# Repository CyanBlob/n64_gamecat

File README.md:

# N64 GameCat

This is a free, open-source implementation of a Nintendo 64 cheating device, akin to the GameShark. It's currently based around the Kendryte K210 SoC (using the Sipeed MAiX BiT breakout), which I chose due to the high number of configurable IO (the N64 cartridge has 50 pins, though many of those aren't necessary for this project). I may eventually add support for ESP32 chips to the GameCat as well.

## Building
This is a PlatformIO project (https://platformio.org/), so building and uploading are relatively straightforward. Simply install PlatformIO (and make sure to add it to your $PATH), and then run `platformio run --target upload --target monitor` with the MAiX BiT plugged in. If it complains about `udev` rules, follow the link it provides.

## Circuits/schematics
I have some test PCBs on order (files are in the `/pcb` directory, made with KiCad EDA). Once I get the design for those finalized it should be as simple as ordering a PCB, soldering the MCU on, and soldering on a cartridge slot
#### Note:
When ordering a cartridge slot, it's important to get one with 2.5mm pin spacing. I've seen several only with 2.54mm spacing, which may not work on this PCB (or with the cartridges in general). I'm using this $2.50 version from AliExpress: https://www.aliexpress.com/item/33002915153.html?spm=a2g0s.9042311.0.0.1ec84c4dN5ezxJ

## FAQ
### Why do this?
I was bored, and that's literally the only reason. If you want to cheat at N64 games, you're likely much better off with an emulator.

### I looked at the PCB. Won't the cartridge end up being parallel with the console if I solder the cartridge slot on it?
Yes.
### Why?
I have no idea what I'm doing.

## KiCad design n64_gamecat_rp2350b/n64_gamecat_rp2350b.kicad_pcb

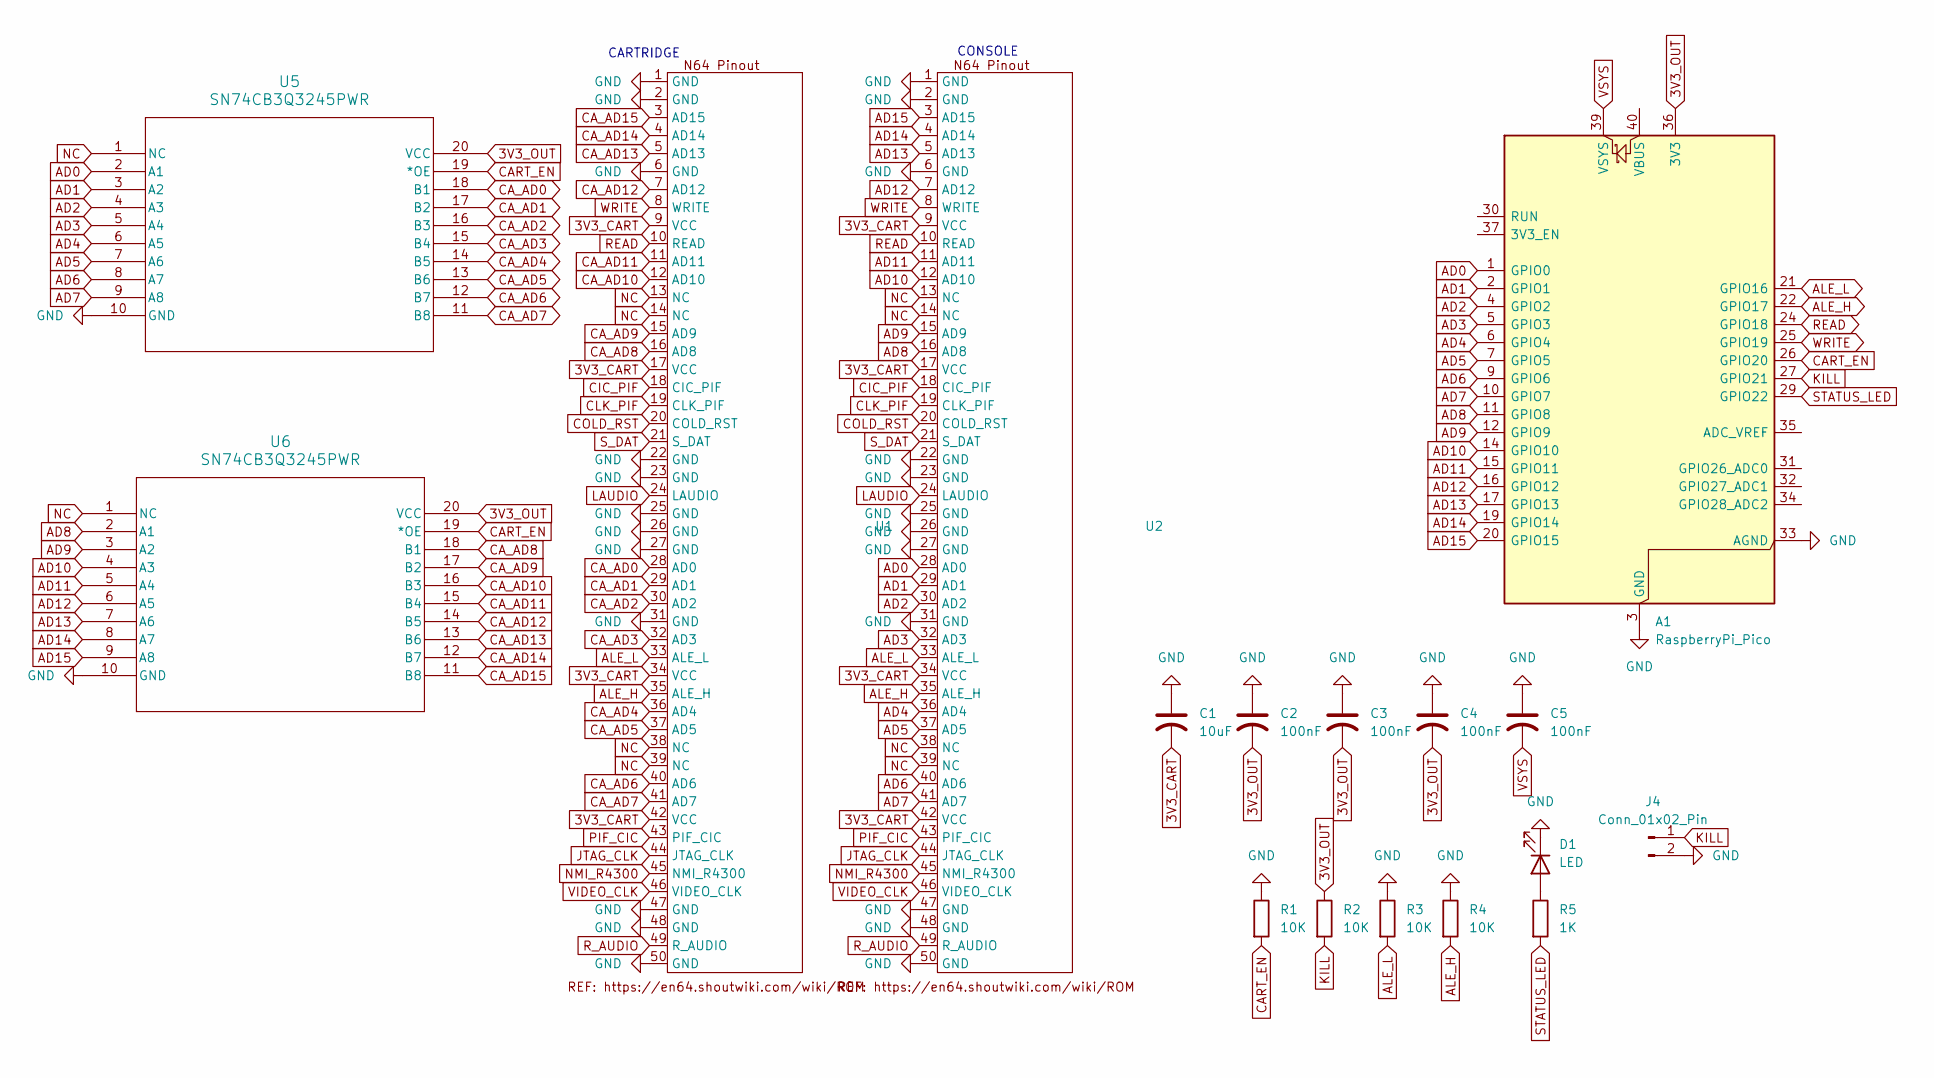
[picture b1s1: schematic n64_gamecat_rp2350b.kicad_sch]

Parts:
A1: RaspberryPi_Pico; RaspberryPi_Pico_Common_Unspecified
C1: 10uF; C_0805_2012Metric
C2, C3, C4, C5: 100nF; C_0402_1005Metric
D1: LED; LED_0402_1005Metric
J4: Conn_01x02_Pin; PinHeader_1x02_P2.54mm_Vertical
R1, R2, R3, R4: 10K; R_0402_1005Metric
R5: 1K; R_0402_1005Metric
U1: N64_cartridge_connecter_2.5mm
U2: N64_cartridge_pins_2.5mm
U5, U6: SN74CB3Q3245PWR; PW20

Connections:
3V3_CART: C1.2, U1.9 (VCC), U1.17 (VCC), U1.34 (VCC), U1.42 (VCC), U2.9 (VCC), U2.17 (VCC), U2.34 (VCC), U2.42 (VCC)
3V3_OUT: A1.36 (3V3), C2.2, C3.2, C4.2, R2.1, U5.20 (VCC), U6.20 (VCC)
AD0: A1.1 (GPIO0), U2.28 (AD0), U5.2 (A1)
AD1: A1.2 (GPIO1), U2.29 (AD1), U5.3 (A2)
AD2: A1.4 (GPIO2), U2.30 (AD2), U5.4 (A3)
AD3: A1.5 (GPIO3), U2.32 (AD3), U5.5 (A4)
AD4: A1.6 (GPIO4), U2.36 (AD4), U5.6 (A5)
AD5: A1.7 (GPIO5), U2.37 (AD5), U5.7 (A6)
AD6: A1.9 (GPIO6), U2.40 (AD6), U5.8 (A7)
AD7: A1.10 (GPIO7), U2.41 (AD7), U5.9 (A8)
AD8: A1.11 (GPIO8), U2.16 (AD8), U6.2 (A1)
AD9: A1.12 (GPIO9), U2.15 (AD9), U6.3 (A2)
AD10: A1.14 (GPIO10), U2.12 (AD10), U6.4 (A3)
AD11: A1.15 (GPIO11), U2.11 (AD11), U6.5 (A4)
AD12: A1.16 (GPIO12), U2.7 (AD12), U6.6 (A5)
AD13: A1.17 (GPIO13), U2.5 (AD13), U6.7 (A6)
AD14: A1.19 (GPIO14), U2.4 (AD14), U6.8 (A7)
AD15: A1.20 (GPIO15), U2.3 (AD15), U6.9 (A8)
ALE_H: A1.22 (GPIO17), R4.2, U1.35 (ALE_H), U2.35 (ALE_H)
ALE_L: A1.21 (GPIO16), R3.2, U1.33 (ALE_L), U2.33 (ALE_L)
CART_EN: A1.26 (GPIO20), R1.2, U5.19 (*OE), U6.19 (*OE)
CA_AD0: U1.28 (AD0), U5.18 (B1)
CA_AD1: U1.29 (AD1), U5.17 (B2)
CA_AD2: U1.30 (AD2), U5.16 (B3)
CA_AD3: U1.32 (AD3), U5.15 (B4)
CA_AD4: U1.36 (AD4), U5.14 (B5)
CA_AD5: U1.37 (AD5), U5.13 (B6)
CA_AD6: U1.40 (AD6), U5.12 (B7)
CA_AD7: U1.41 (AD7), U5.11 (B8)
CA_AD8: U1.16 (AD8), U6.18 (B1)
CA_AD9: U1.15 (AD9), U6.17 (B2)
CA_AD10: U1.12 (AD10), U6.16 (B3)
CA_AD11: U1.11 (AD11), U6.15 (B4)
CA_AD12: U1.7 (AD12), U6.14 (B5)
CA_AD13: U1.5 (AD13), U6.13 (B6)
CA_AD14: U1.4 (AD14), U6.12 (B7)
CA_AD15: U1.3 (AD15), U6.11 (B8)
CIC_PIF: U1.18 (CIC_PIF), U2.18 (CIC_PIF)
CLK_PIF: U1.19 (CLK_PIF), U2.19 (CLK_PIF)
COLD_RST: U1.20 (COLD_RST), U2.20 (COLD_RST)
GND: A1.3 (GND), A1.8 (GND), A1.13 (GND), A1.18 (GND), A1.23 (GND), A1.28 (GND), A1.33 (AGND), A1.38 (GND), C1.1, C2.1, C3.1, C4.1, C5.1, D1.1 (K), J4.2, R1.1, R3.1, R4.1, U1.1 (GND), U1.2 (GND), U1.6 (GND), U1.22 (GND), U1.23 (GND), U1.25 (GND), U1.26 (GND), U1.27 (GND), U1.31 (GND), U1.47 (GND), U1.48 (GND), U1.50 (GND), U2.1 (GND), U2.2 (GND), U2.6 (GND), U2.22 (GND), U2.23 (GND), U2.25 (GND), U2.26 (GND), U2.27 (GND), U2.31 (GND), U2.47 (GND), U2.48 (GND), U2.50 (GND), U5.10 (GND), U6.10 (GND)
JTAG_CLK: U1.44 (JTAG_CLK), U2.44 (JTAG_CLK)
KILL: A1.27 (GPIO21), J4.1, R2.2
LAUDIO: U1.24 (LAUDIO), U2.24 (LAUDIO)
NC: U1.13 (NC), U1.14 (NC), U1.38 (NC), U1.39 (NC), U2.13 (NC), U2.14 (NC), U2.38 (NC), U2.39 (NC), U5.1 (NC), U6.1 (NC)
NMI_R4300: U1.45 (NMI_R4300), U2.45 (NMI_R4300)
unnamed: D1.2 (A), R5.1
PIF_CIC: U1.43 (PIF_CIC), U2.43 (PIF_CIC)
READ: A1.24 (GPIO18), U1.10 (READ), U2.10 (READ)
R_AUDIO: U1.49 (R_AUDIO), U2.49 (R_AUDIO)
STATUS_LED: A1.29 (GPIO22), R5.2
S_DAT: U1.21 (S_DAT), U2.21 (S_DAT)
VIDEO_CLK: U1.46 (VIDEO_CLK), U2.46 (VIDEO_CLK)
VSYS: A1.39 (VSYS), C5.2
WRITE: A1.25 (GPIO19), U1.8 (WRITE), U2.8 (WRITE)

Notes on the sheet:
CONSOLE
CARTRIDGE

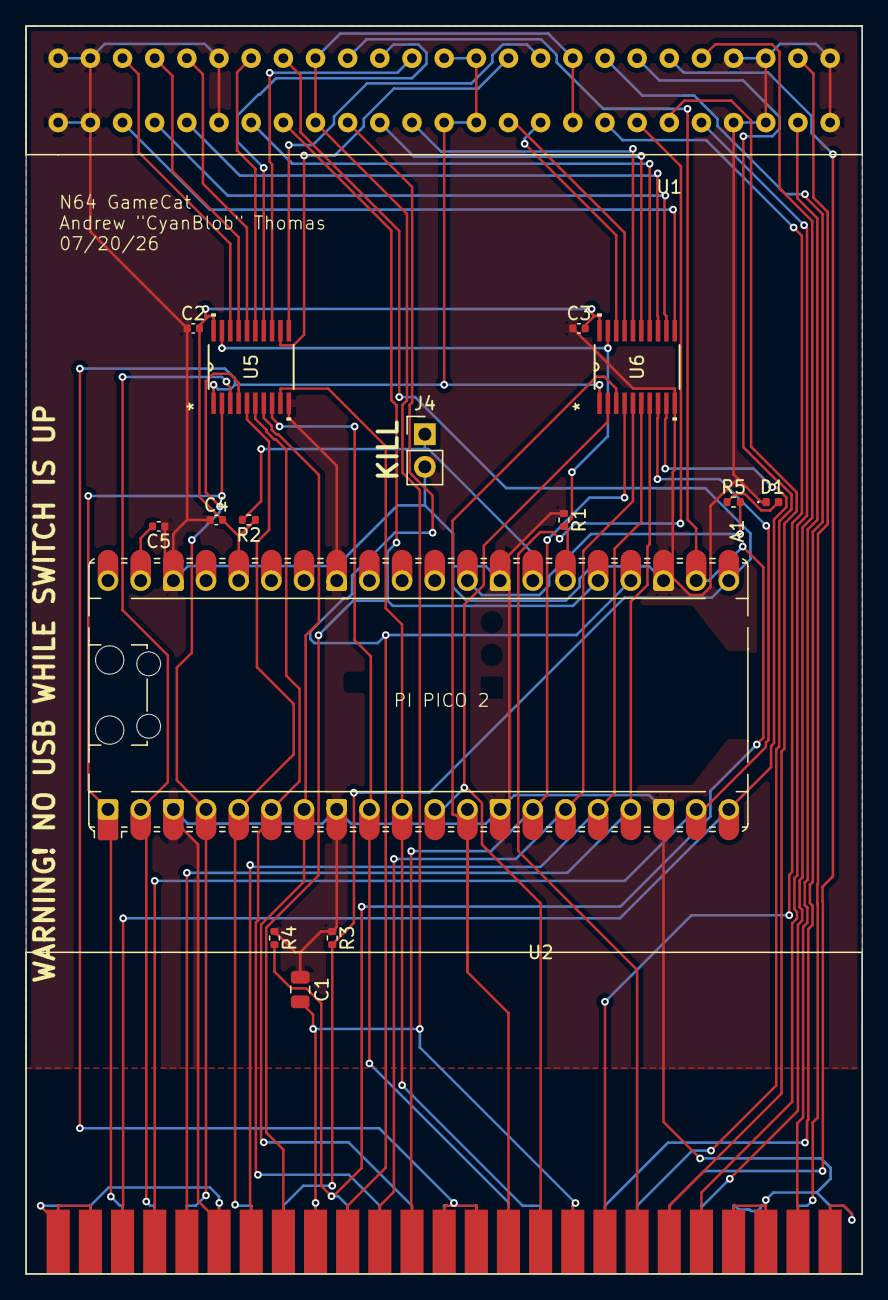
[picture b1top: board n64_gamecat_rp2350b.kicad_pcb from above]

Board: 2 copper layers, 65.0 x 97.0 mm, 17 parts (0 on the bottom side), 55 nets.

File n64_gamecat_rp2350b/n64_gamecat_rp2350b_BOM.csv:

"Id";"Designator";"Footprint";"Quantity";"Designation";"Supplier and ref";
1;"A1";"RaspberryPi_Pico_Common_Unspecified";1;"RaspberryPi_Pico";;;
2;"C1";"C_0805_2012Metric";1;"10uF";;;
3;"C2, C3, C4, C5";"C_0402_1005Metric";4;"100nF";;;
4;"D1";"LED_0402_1005Metric";1;"LED";;;
5;"J4";"PinHeader_1x02_P2.54mm_Vertical";1;"Conn_01x02_Pin";;;
6;"R1, R2, R3, R4";"R_0402_1005Metric";4;"10K";;;
7;"R5";"R_0402_1005Metric";1;"1K";;;
8;"SW1";"PinSocket_1x03_P2.54mm_Vertical";1;"SW_SPDT";;;
9;"U1";"N64_cartridge_connecter_2.5mm";1;"~";;;
10;"U2";"N64_cartridge_pins_2.5mm";1;"~";;;
11;"U3, U4";"DW20";2;"SN74CBTLV3245ADW";;;

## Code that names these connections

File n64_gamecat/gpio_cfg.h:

#ifndef N64_GAMECAT_GPIO_CFG_H
#define N64_GAMECAT_GPIO_CFG_H

#define PIN_MIN  2
#define PIN_MAX  39

#define CA_AD0  2
#define CA_AD1  3
#define CA_AD2  4
#define CA_AD3  5
#define CA_AD4  6
#define CA_AD5  7
#define CA_AD6  8
#define CA_AD7  9
#define CA_AD8  10
#define CA_AD9  11
#define CA_AD10 12
#define CA_AD11 13
#define CA_AD12 14
#define CA_AD13 15
#define CA_AD14 16
#define CA_AD15 17

#define CO_AD0  18
#define CO_AD1  19
#define CO_AD2  20
#define CO_AD3  21
#define CO_AD4  22
#define CO_AD5  23
#define CO_AD6  24
#define CO_AD7  25
#define CO_AD8  26
#define CO_AD9  27
#define CO_AD10 28
#define CO_AD11 29
#define CO_AD12 30
#define CO_AD13 31
#define CO_AD14 32
#define CO_AD15 33

uint console_pins[] = {

        CO_AD0,
        CO_AD1,
        CO_AD2,
        CO_AD3,
        CO_AD4,
        CO_AD5,
        CO_AD6,
        CO_AD7,
        CO_AD8,
        CO_AD9,
        CO_AD10,
        CO_AD11,
        CO_AD12,
        CO_AD13,
        CO_AD14,
        CO_AD15,
};
uint cartridge_pins[] = {
        CA_AD0,
        CA_AD1,
        CA_AD2,
        CA_AD3,
        CA_AD4,
        CA_AD5,
        CA_AD6,
        CA_AD7,
        CA_AD8,
        CA_AD9,
        CA_AD10,
        CA_AD11,
        CA_AD12,
        CA_AD13,
        CA_AD14,
        CA_AD15,
};

#define ALE_H 34
#define ALE_L 35
#define WRITE 36
#define READ  37

#define FLAG_ALE_H 40
#define FLAG_ALE_L 41
#define FLAG_WRITE 42
#define FLAG_READ 43

#endif //N64_GAMECAT_GPIO_CFG_H

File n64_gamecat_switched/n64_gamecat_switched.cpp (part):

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
/* ========= Pin mapping ========= */
#define AD_BASE         0   // GPIO N..N+15 -> AD[0..15]
#define CART_EN_PIN     20   // sideset to CBT OE/EN (1=connected, 0=isolated)
#define KILL_PIN        21   // pull low to force pass-through
#define STATUS_LED_PIN  22   // D1 on the schematic (heartbeat)

#define ALE_L_PIN_REL   16
#define ALE_H_PIN_REL   17
#define READ_N_PIN_REL  18
#define WRITE_N_PIN_REL 19
#define ALE_L_GPIO      (AD_BASE + ALE_L_PIN_REL)
#define ALE_H_GPIO      (AD_BASE + ALE_H_PIN_REL)
#define READ_N_GPIO     (AD_BASE + READ_N_PIN_REL)
#define WRITE_N_GPIO    (AD_BASE + WRITE_N_PIN_REL)

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    #if DEBUG_PRINT
    printf("heartbeat: %d\n", state);
    #endif
    gpio_put(STATUS_LED_PIN, state);
    return true; // keep firing
}

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
int main_dumb() {
    stdio_init_all();
    gpio_init(CART_EN_PIN);
    gpio_set_dir(CART_EN_PIN, true);
    gpio_put(CART_EN_PIN, 0);   // CBT closed, cart connected

    // Heartbeat so we know it's alive
    gpio_init(STATUS_LED_PIN);
    gpio_set_dir(STATUS_LED_PIN, true);
    static repeating_timer_t t;
    add_repeating_timer_ms(2000, led_heartbeat_cb, NULL, &t);

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    }

    // Strobes are always inputs from the console.
    gpio_init(ALE_L_GPIO);  gpio_set_dir(ALE_L_GPIO, false);  gpio_pull_down(ALE_L_GPIO);
    gpio_init(ALE_H_GPIO);  gpio_set_dir(ALE_H_GPIO, false);  gpio_pull_down(ALE_H_GPIO);
    gpio_init(READ_N_GPIO); gpio_set_dir(READ_N_GPIO, false);
    gpio_init(WRITE_N_GPIO); gpio_set_dir(WRITE_N_GPIO, false);

    gpio_init(KILL_PIN);    gpio_pull_up(KILL_PIN);
    gpio_init(CART_EN_PIN); gpio_set_dir(CART_EN_PIN, true); gpio_put(CART_EN_PIN, 0);

    // Status LED (D1) — driven by hardware-timer IRQ (see led_heartbeat_cb).
    gpio_init(STATUS_LED_PIN);
    gpio_set_dir(STATUS_LED_PIN, true);
    gpio_put(STATUS_LED_PIN, 0);
    static repeating_timer_t heartbeat_timer;
    add_repeating_timer_ms(HEARTBEAT_PERIOD_MS, led_heartbeat_cb, NULL, &heartbeat_timer);

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
    // Responder owns AD (for driving) and CART_EN (for sideset).
    for (int i = 0; i < 16; ++i) pio_gpio_init(pio_rsp, AD_BASE + i);
    pio_gpio_init(pio_rsp, CART_EN_PIN);

    // CART_EN must be an output from the PIO's perspective; AD starts as input
    // (cart drives until we isolate and override).
    pio_sm_set_consecutive_pindirs(pio_rsp, sm_rsp, CART_EN_PIN, 1, true);
    pio_sm_set_consecutive_pindirs(pio_rsp, sm_rsp, AD_BASE, 16, false);

    // Capture SM config
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        pio_sm_config c = n64_respond_tokens_program_get_default_config(off_rsp);
        sm_config_set_out_pins(&c, AD_BASE, 16);
        sm_config_set_in_pins(&c, AD_BASE);
        sm_config_set_sideset_pins(&c, CART_EN_PIN);
        // shift_right so `out x, 16` / `out y, 16` unpack SKIP then DATA.
        // autopull MUST be false: the program already does explicit `pull
        // block`, and our two `out` instructions consume exactly 32 bits
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

    #if DEBUG_PRINT
    printf("Killed: %d\n", !gpio_get(KILL_PIN));
    #endif

    // DEBUG: after a burst fires a rule, trace the raw sequence of every
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        // until the reset below clears it — telling us definitively whether
        // the previous burst left the cart isolated or safely idle
        // (side0/skip_loop), without needing another LA capture.
        bool prev_cart_isolated = gpio_get(CART_EN_PIN);

        if (trace_remaining > 0) {
            printf("[trace t=%llu us] addr=0x%08X  prev_cart_isolated=%d\n",
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        // arrive (up to ~2ms/halfword timeouts), which previously ran
        // *before* this and desynced the skip count enough that overrides
        // landed on the wrong, later burst instead of the intended one.
        bool killed = !gpio_get(KILL_PIN);
        if (!killed) {
            uint32_t base_word  = base_addr & ~0x3u;
            // Verified against a live capture of the cart header: for a
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
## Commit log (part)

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2020-08-29 Initial firmware upload; should be able to read/write (not save), while overriding one ROM value
2020-08-29 Add PCB files
2020-08-29 Add README.md
2020-08-29 Add GLPv2 license
2020-09-03 Use pins other than 31-35, since they can't be used as GPIOHS
2020-09-03 Generate version 0.2 PCB Gerber files
2021-02-19 Add rev 3 PCB
2021-02-20 Add initial Vivado project for FPGA
2021-02-21 Add simulation; improve FPGA logic
2021-02-21 Source file cleanup
2021-02-21 File cleanup
2021-03-26 Stop using seperate clock signal
2021-06-26 Improve simulation
2021-06-26 FBGA source rewrite; still broken
2024-03-16 Fix read logic
2024-10-18 2024 rewrite
2024-10-29 V0.6 PCB
2024-11-01 v0.7 PCB; prep for 2350
2024-11-02 Add v0.8 PCB
2024-11-02 Add GPIO init
2024-11-02 Start adding state machine
2024-12-27 Start adding software; add data plotter; add real .8 gerber
2024-12-27 Improve sample rate
2024-12-27 Add reminder for switching to SIO instead of GPIO coprocessor
2025-01-17 Add v0.9 PCB
2025-01-17 Initial PIO <-> DMA implementation
2025-09-15 Updates to improve DMA
2025-09-16 Yet another rewrite and redesign
2026-04-17 Finish switched implementation
2026-04-25 Misc changes; add OoT decomp
2026-05-05 Add binary_patcher host tool for ROM string/hex patching
    Searches an N64 ROM for text or hex patterns defined in a JSON rules file,
    writes a patched binary (for emulator/reference use), and generates a C header
    with patch_rule_t entries the MCU firmware can #include to intercept the same
    addresses at runtime without touching flash.
    - Auto-detects and normalises z64/v64/n64 ROM byte-order formats
    - One MCU rule per changed 4-byte aligned cart-bus word; unchanged bytes in
2026-05-05 Add __pycache__ and *.pyc to .gitignore
    Suppresses Python bytecode cache generated by the new binary_patcher tool.
    https://claude.ai/code/session_01U7tmvpVvf7K6Mod25EMBYM
